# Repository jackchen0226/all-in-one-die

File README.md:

<h3 align="center">ECE 411 Practicum Project</h3>

<p align="center">
  Practicum Project for Team 3 (Fall 2020)
  <br>
  <a href="https://github.com/jackchen0226/all-in-one-die/wiki"><strong>Team Wiki »</strong></a>
  <br>
  <br>
</p>

## Table of contents

- [Status](#status)
- [Overview](#overview)
- [Documentation](#documentation)
- [Creators](#creators)

## Status

All aspects are currently being developed, reviewed, and tested.

## Overview

All-in-One-Die is an extra-large die that you can shake with your own two hands! Large enough to be larger than your average d6 or d20, and it ‘rolls’ when you shake it. Additionally, when a 1 is rolled, an extremely negative sound will be played. This is for those who enjoy tabletop gaming and want a fun novelty item that is interactive.

Not family-friendly may involve swearing

## Documentation

Will be included upon completion.

## Creators

Hannah Mortimer (hmort2@pdx.edu) <br />
Devon Mickels (dmickels@pdx.edu) <br />
Nicole Fellows  (nicol27@pdx.edu) <br />
Jack Chen (chenjac@pdx.edu)

## 3 Brainstormed Ideas:

All-in-one-die  <br />
Farmbot <br />
Replacement Piano Key <br />

Please look at the [project ideas](https://github.com/jackchen0226/all-in-one-die/wiki/Project-Ideas) for full descriptions of all 3 ideas!

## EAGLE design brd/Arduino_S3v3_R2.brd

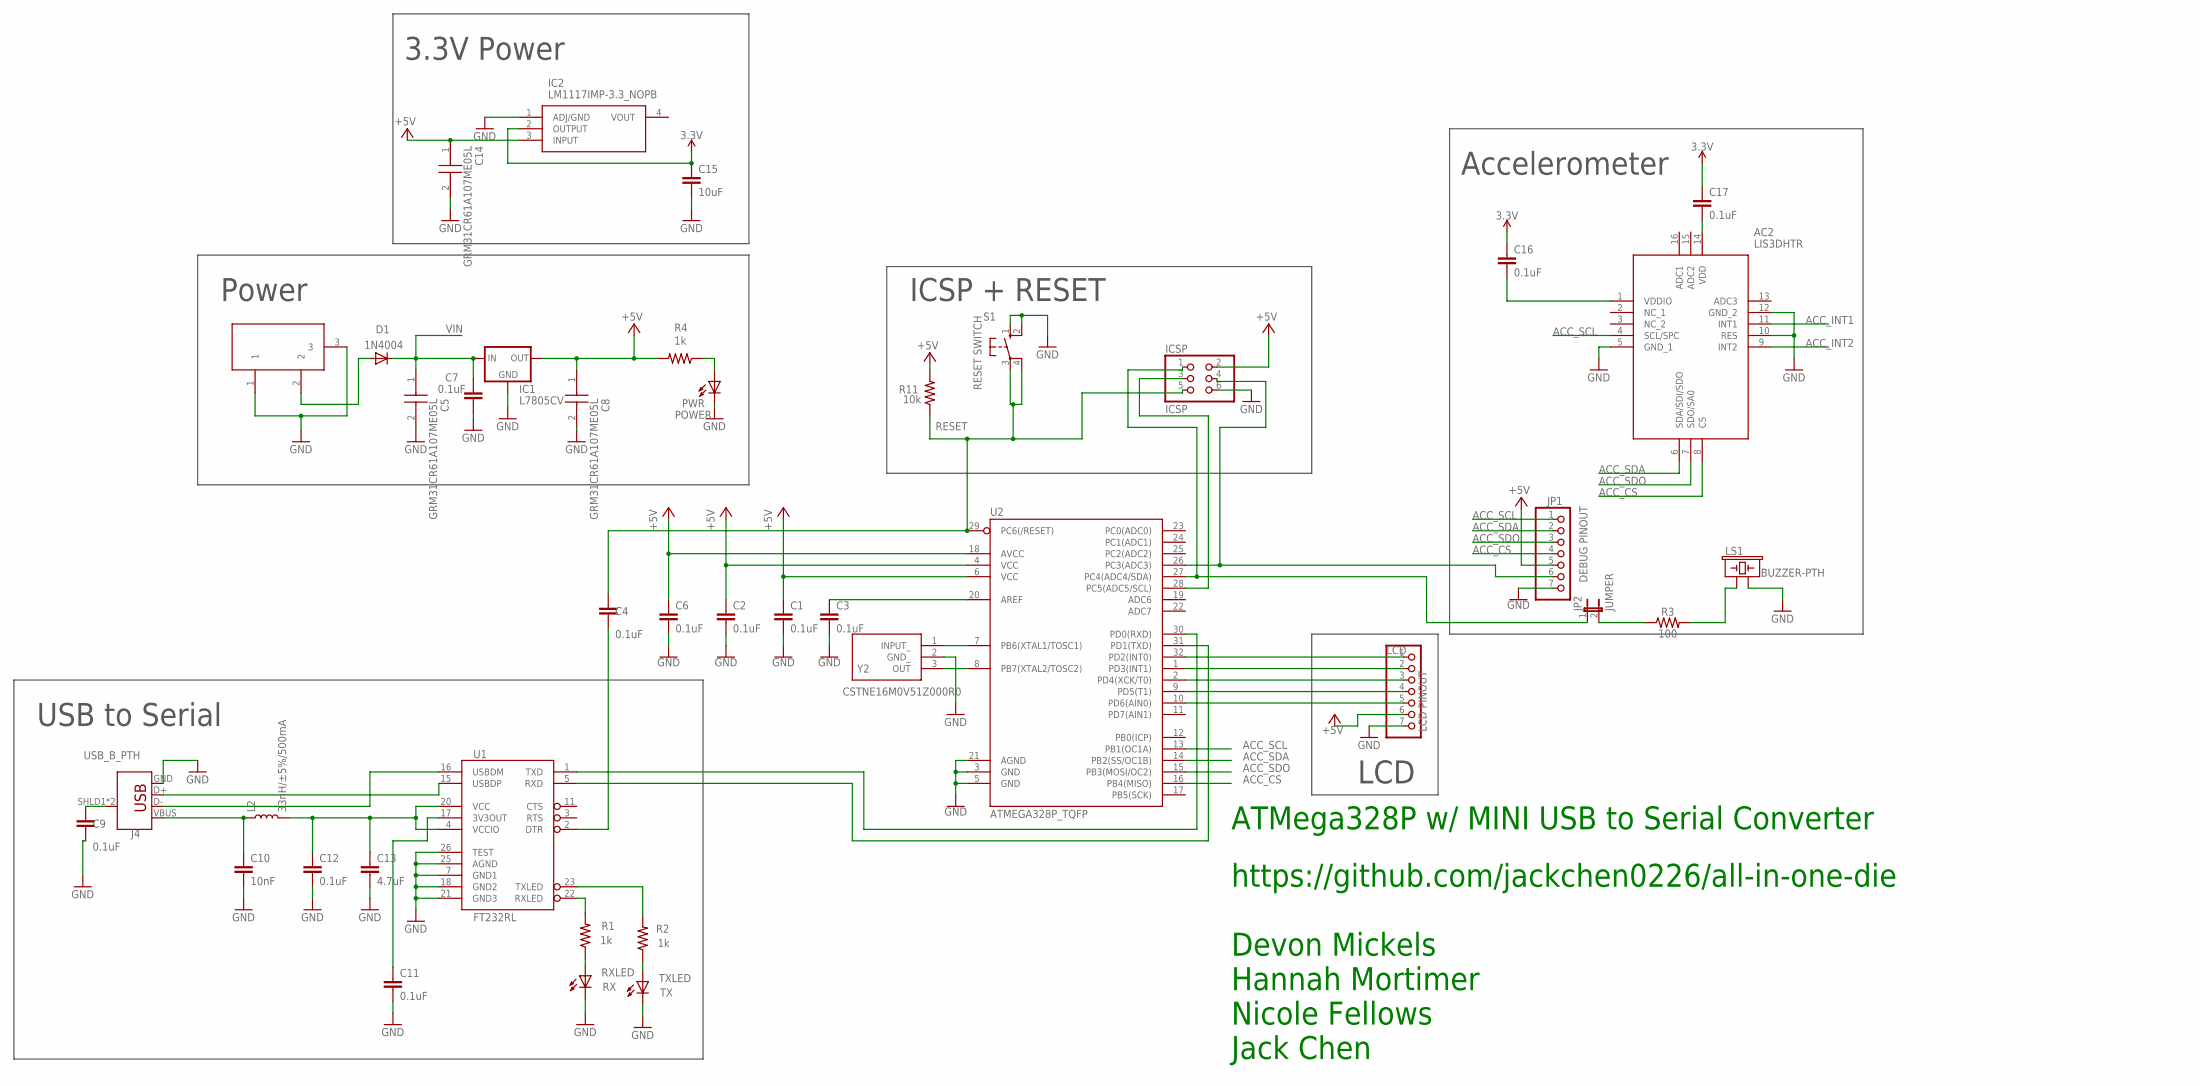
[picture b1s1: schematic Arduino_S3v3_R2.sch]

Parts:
AC2: LIS3DHTR
C1, C2, C3, C4, C6, C7, C9, C11, C12, C16, C17: 0.1uF; 0603; MPN C0603X104K5RAC3316
C5, C8, C14: GRM31CR61A107ME05L; CAPC3216X180N
C10: 10nF; 0603; MPN C0603C103K5RAC7013
C13: 4.7uF; 0603; MPN LMK107BJ475MAHT
C15: 10uF; 0603; MPN GRM188R61E106KA73D
D1: 1N4004; DO41-10; MPN 1N4004-T
DC1: DC21MMX; DC-21MM; MPN CON-SOCJ-2155
IC1: L7805CV; 78XXS; MPN L7805CV
IC2: LM1117IMP-3.3_NOPB; SOT230P700X180-4N
ICSP: ICSP; 2X03; MPN M20-9980346
J4: USB_B_PTH; USB-B-PTH; MPN 61729-0010BLF
JP1: DEBUG PINOUT; 1X07; MPN M20-9770746
JP2: JUMPER; JP1; MPN M20-9990246
L2: 33nH/±5%/500mA; 0603; MPN LQW18AS33NJ0CD
LCD: LCD PINOUT; 1X07; MPN M20-9770746
LS1: BUZZER-PTH; BUZZER-12MM; MPN SD1209T5-A1
PWR: POWER; LED3MM; MPN LTH3MM12VFR4100
R1, R2, R4: 1k; 0603; MPN RCC06031K00FKEA
R3: 100; 0603; MPN RCC0603100RFKEA
R11: 10k; 0603; MPN ERJ-UP3D1002V
RXLED: RX; LED3MM; MPN LTH3MM12VFR4500
S1: RESET SWITCH; B3F-10XX; MPN B3F-1000
TXLED: TX; LED3MM; MPN LTH3MM12VFR4500
U1: FT232RL; SSOP28DB; MPN FT232RL-REEL
U2: ATMEGA328P_TQFP; TQFP32-08; MPN ATMEGA328P-AU
Y2: CSTNE16M0V51Z000R0

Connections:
3.3V: C15.1, C16.1, C17.1, IC2.2 (OUTPUT)
+5V: C1.1, C2.1, C6.1, C8.1, C14.1, IC1.OUT, IC2.3 (INPUT), ICSP.2, JP1.5, LCD.6, R4.2, R11.2, U2.4 (VCC), U2.6 (VCC), U2.18 (AVCC)
ACC_CS: AC2.8 (CS), JP1.4, U2.16 (PB4(MISO))
ACC_INT1: AC2.11 (INT1)
ACC_INT2: AC2.9 (INT2)
ACC_SCL: AC2.4 (SCL/SPC), JP1.1, U2.13 (PB1(OC1A))
ACC_SDA: AC2.6 (SDA/SDI/SDO), JP1.2, U2.14 (PB2(SS/OC1B))
ACC_SDO: AC2.7 (SDO/SA0), JP1.3, U2.15 (PB3(MOSI/OC2))
BUZZ: ICSP.1, JP2.1, U2.27 (PC4(ADC4/SDA))
GND: AC2.5 (GND_1), AC2.10 (RES), AC2.12 (GND_2), C1.2, C2.2, C3.2, C5.2, C6.2, C7.1, C8.2, C9.2, C10.2, C11.2, C12.2, C13.2, C14.2, C15.2, DC1.1, DC1.3, IC1.GND, IC2.1 (ADJ/GND), ICSP.6, J4.GND, JP1.7, LCD.7, LS1.- (2), PWR.K (C), RXLED.K (C), S1.1 (S), S1.2 (S1), TXLED.K (C), U1.7 (GND1), U1.18 (GND2), U1.21 (GND3), U1.25 (AGND), U1.26 (TEST), U2.3 (GND), U2.5 (GND), U2.21 (AGND), Y2.2 (GND_)
LCD_CS: LCD.1, U2.32 (PD2(INT0))
LCD_SCL: LCD.4, U2.9 (PD5(T1))
LCD_SDA: LCD.3, U2.2 (PD4(XCK/T0))
LCD_SDO: LCD.2, U2.1 (PD3(INT1))
unnamed: U2.7 (PB6(XTAL1/TOSC1)), Y2.1 (INPUT_)
unnamed: C9.1, J4.SHLD1 (SHIELD), J4.SHLD2 (SHIELD)
unnamed: PWR.A, R4.1
unnamed: C4.2, U1.2 (DTR)
unnamed: AC2.14 (VDD), C17.2
unnamed: U2.8 (PB7(XTAL2/TOSC2)), Y2.3 (OUT)
unnamed: AC2.1 (VDDIO), C16.2
unnamed: D1.A, DC1.2
unnamed: J4.D+, U1.15 (USBDP)
unnamed: LCD.5, U2.10 (PD6(AIN0))
unnamed: JP2.2, R3.1
unnamed: LS1.+ (1), R3.2
unnamed: ICSP.3, U2.28 (PC5(ADC5/SCL))
unnamed: C3.1, U2.20 (AREF)
unnamed: C11.1, U1.17 (3V3OUT)
unnamed: J4.D-, U1.16 (USBDM)
unnamed: C10.1, J4.VBUS, L2.1
unnamed: R2.1, TXLED.A
unnamed: R1.1, RXLED.A
POTIN: ICSP.4, JP1.6, U2.26 (PC3(ADC3))
RESET: C4.1, ICSP.5, R11.1, S1.3, S1.4 (P1), U2.29 (PC6(/RESET))
RXD: U1.5 (RXD), U2.31 (PD1(TXD))
RXLED: R1.2, U1.22 (RXLED)
TXD: U1.1 (TXD), U2.30 (PD0(RXD))
TXLED: R2.2, U1.23 (TXLED)
VBUS: C12.1, C13.1, L2.2, U1.4 (VCCIO), U1.20 (VCC)
VIN: C5.1, C7.2, D1.C, IC1.IN

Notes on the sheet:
https://github.com/jackchen0226/all-in-one-die Devon Mickels Hannah Mortimer Nicole Fellows Jack Chen
ATMega328P w/ MINI USB to Serial Converter
Power
USB to Serial
ICSP + RESET
Accelerometer
LCD
3.3V Power

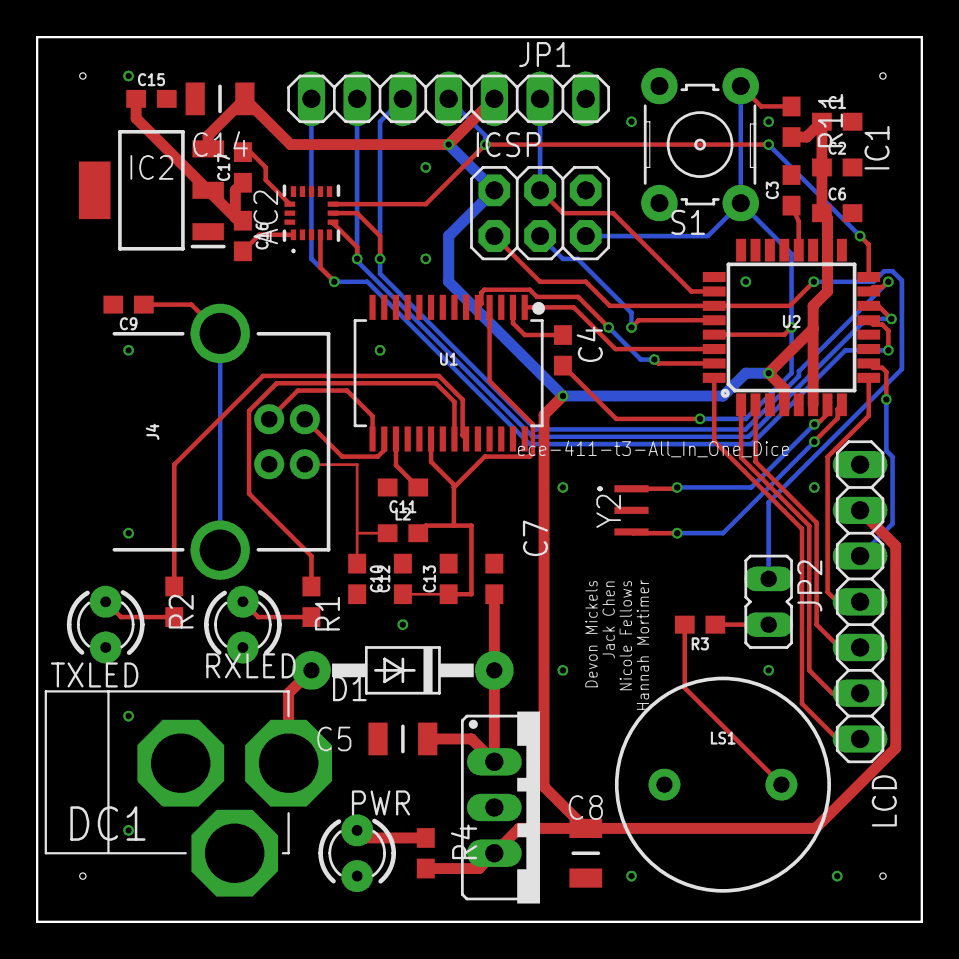
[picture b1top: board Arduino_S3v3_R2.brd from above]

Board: 2 copper layers, 49.1 x 49.1 mm, 41 parts (0 on the bottom side), 39 nets.

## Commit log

2020-10-10 Added license
2020-10-10 Create test.md
    created test for a documents directory
2020-10-10 Moved File
    Moved Project Ideas to Documents Folder
2020-10-10 Removed Documentation folder
2020-10-10 init code
2020-10-15 Created base code base
2020-11-05 Added EagleCAD files.
2020-11-10 Added buzzer, adjusted for SPI, new accel, pot in
2020-11-10 Board design final dimensions. Rough Draft ready.
2020-11-12 Thickened lines for board outline to width 5
2020-11-12 Added initial manufacturing part numbers
2020-11-12 updated to SPI, replaced TH comps, new accel
    New accelerometer is not hooked up yet.
2020-11-14 Added documents for project schedule
2020-11-14 new accel, 3.3v regulator, final draft
    Ready for Board Review.
2020-11-14 Added notes from design review on 2020-11-14
2020-11-15 Modified according to Desgin Review w/ Greenberg
2020-11-16 Modified after meeting w/ Team 13
2020-11-18 Added BOM files
2020-11-18 Updated schematic with MPNS, MFRs for pin headers and others
2020-11-18 Update .replit
    Current version of code 11/18/2020
2020-11-18 Moved board name to center of the board
2020-11-19 Added System Design doc
2020-11-20 updated system design doc
2020-11-21 Clean up defines for source file, moved to src/
2020-12-07 Added implementation for an ESP32
2020-12-07 Removed deprecated code
2020-12-07 RNG now seeded with 3 real-world sources (pos, accel, analog read)
2020-12-08 Added and renamed documentation files. Included revision numbers on files
2020-12-08 Added images of the latest version of board layer + schematic
2020-12-08 Added README to redirect to wiki for documentation
2020-12-08 Added testing information for unit testing of modules
2020-12-08 Added testcase for randomness generation
2020-12-08 Added extensive test case documents + template
2020-12-09 Added new buzzer test, fixed typo in accelerometer test
2020-12-09 Added define for maximum value of ADC
2020-12-09 Added extra comments for ESP32 and Uno/atmega differences
2020-12-09 Fixed binning of pot on ADC, changed defines for Uno/atmega
2020-12-09 Add files via upload
    STL files for the holder.

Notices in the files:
parts and their libraries:
SparkFun-Capacitors: Licensing: Creative Commons ShareAlike 4.0 International - https://creativecommons.org/licenses/by-sa/4.0
